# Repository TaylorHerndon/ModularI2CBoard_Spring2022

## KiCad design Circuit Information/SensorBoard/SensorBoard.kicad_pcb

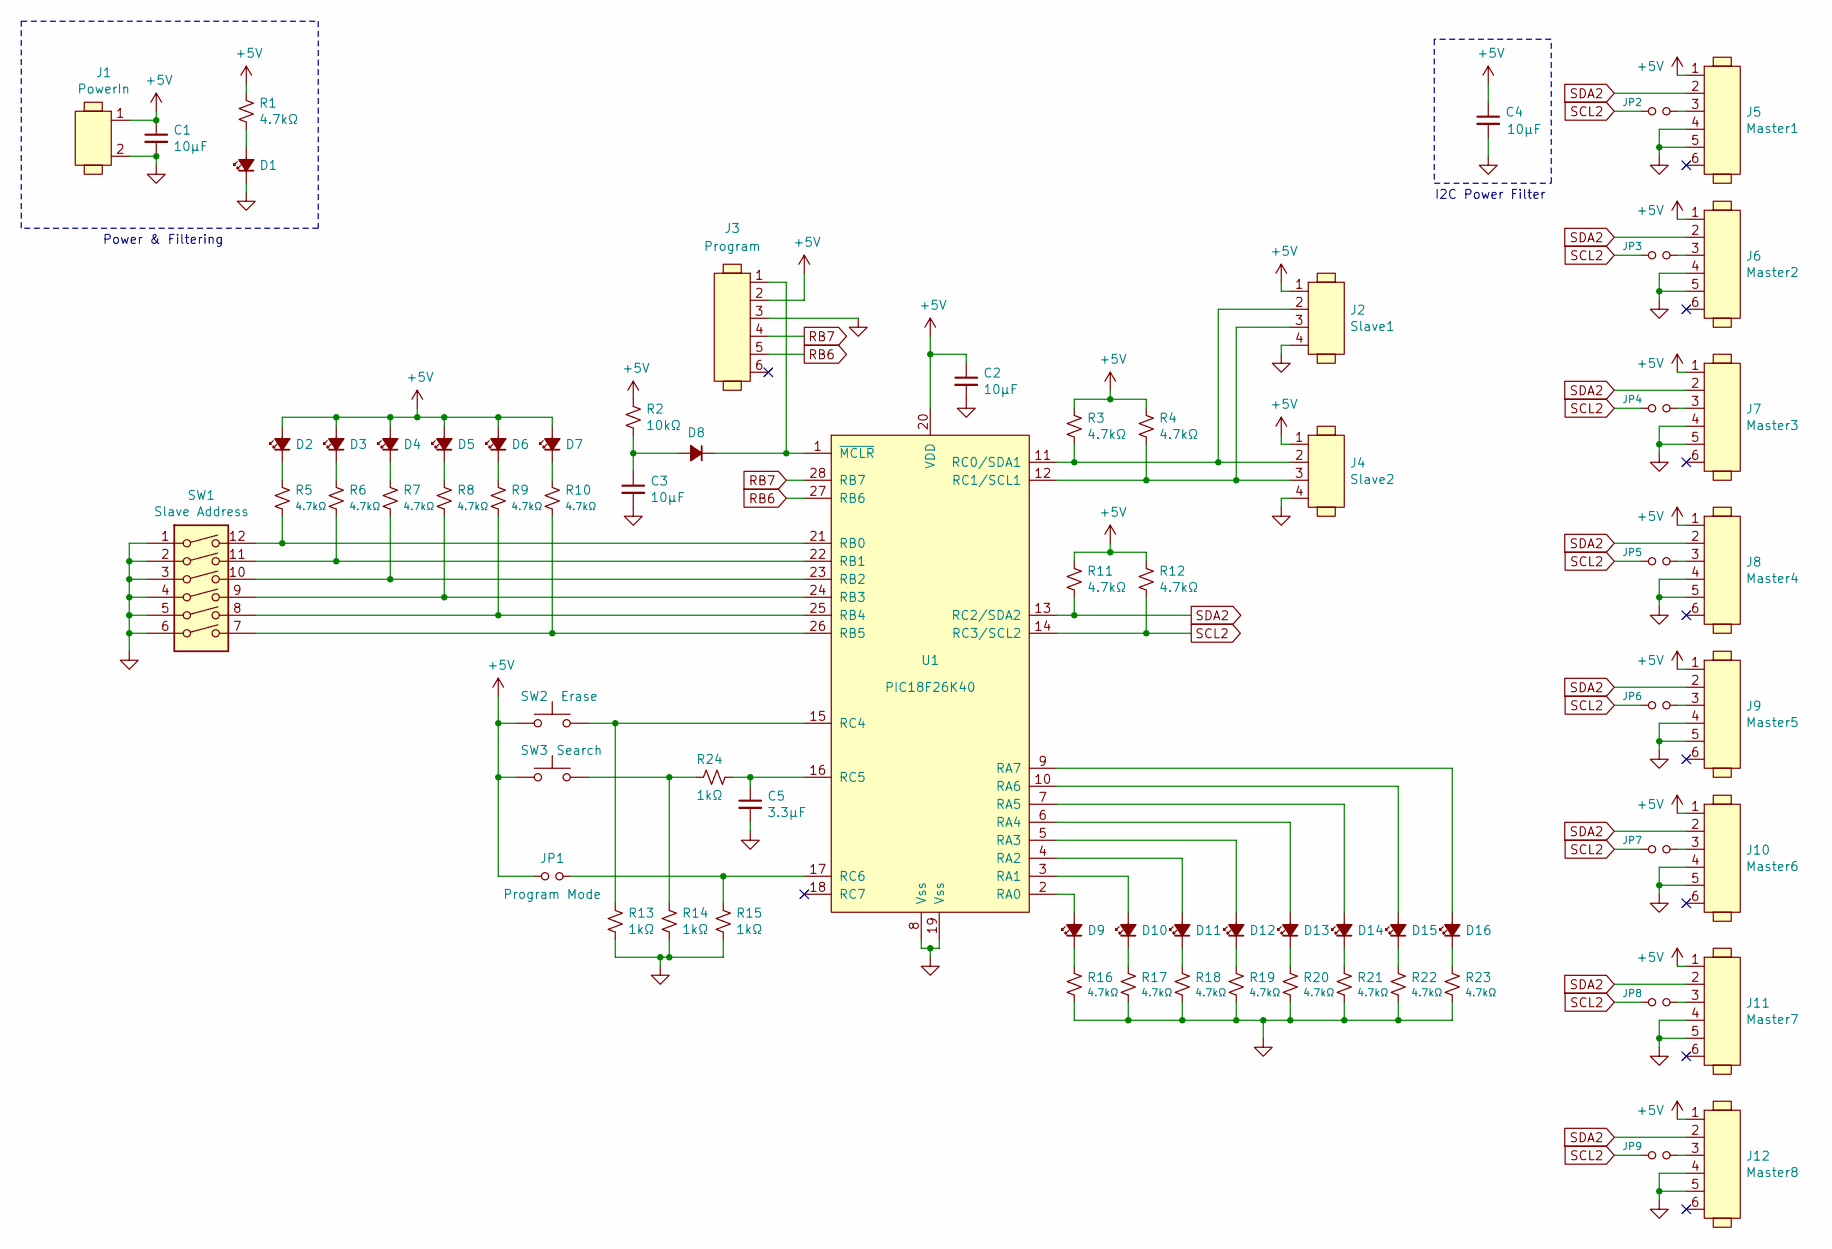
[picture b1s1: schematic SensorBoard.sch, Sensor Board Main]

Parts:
C1, C2, C3, C4: 10µF; R_0805_2012Metric_Pad1.20x1.40mm_HandSolder
C5: 3.3µF; R_0805_2012Metric_Pad1.20x1.40mm_HandSolder
D1, D2, D3, D4, D5, D6, D7, D9, D10, D11, D12, D13, D14, D15, D16: LED_Small_ALT; D_0805_2012Metric
D8: D_Small_ALT; D_0805_2012Metric
J1: PowerIn; 2PinScrewTerminal
J2: Slave1; Molex_KK-254_AE-6410-04A_1x04_P2.54mm_Vertical
J3: Program; PinHeader_1x06_P2.54mm_Vertical
J4: Slave2; Molex_KK-254_AE-6410-04A_1x04_P2.54mm_Vertical
J5: Master1; Molex_KK-254_AE-6410-06A_1x06_P2.54mm_Vertical
J6: Master2; Molex_KK-254_AE-6410-06A_1x06_P2.54mm_Vertical
J7: Master3; Molex_KK-254_AE-6410-06A_1x06_P2.54mm_Vertical
J8: Master4; Molex_KK-254_AE-6410-06A_1x06_P2.54mm_Vertical
J9: Master5; Molex_KK-254_AE-6410-06A_1x06_P2.54mm_Vertical
J10: Master6; Molex_KK-254_AE-6410-06A_1x06_P2.54mm_Vertical
J11: Master7; Molex_KK-254_AE-6410-06A_1x06_P2.54mm_Vertical
J12: Master8; Molex_KK-254_AE-6410-06A_1x06_P2.54mm_Vertical
JP1: Program Mode; PinHeader_1x02_P2.54mm_Vertical
JP2, JP3, JP4, JP5, JP6, JP7, JP8, JP9: Jumper_NO_Small; PinHeader_1x02_P2.54mm_Vertical
R1, R3, R4, R5, R6, R7, R8, R9, R10, R11, R12, R16, R17, R18, R19, R20, R21, R22, R23: 4.7kΩ; R_0805_2012Metric_Pad1.20x1.40mm_HandSolder
R2: 10kΩ; R_0805_2012Metric_Pad1.20x1.40mm_HandSolder
R13, R14, R15, R24: 1kΩ; R_0805_2012Metric_Pad1.20x1.40mm_HandSolder
SW1: Slave Address; SW_DIP_SPSTx06_Slide_9.78x17.42mm_W7.62mm_P2.54mm
SW2: Erase; SW_PUSH_6mm
SW3: Search; SW_PUSH_6mm
U1: PIC18F26K40; PIC18F26K40-SOIC-28

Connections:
+5V: C1.1, C2.1, C4.1, D2.2 (A), D3.2 (A), D4.2 (A), D5.2 (A), D6.2 (A), D7.2 (A), J1.1, J2.1, J3.2, J4.1, J5.1, J6.1, J7.1, J8.1, J9.1, J10.1, J11.1, J12.1, JP1.1, R1.1, R2.1, R3.1, R4.1, R11.1, R12.1, SW2.1, SW3.1, U1.20 (VDD)
GND: C1.2, C2.2, C3.2, C4.2, C5.2, D1.1 (K), J1.2, J2.4, J3.3, J4.4, J5.4, J5.5, J6.4, J6.5, J7.4, J7.5, J8.4, J8.5, J9.4, J9.5, J10.4, J10.5, J11.4, J11.5, J12.4, J12.5, R13.2, R14.2, R15.2, R16.2, R17.2, R18.2, R19.2, R20.2, R21.2, R22.2, R23.2, SW1.1, SW1.2, SW1.3, SW1.4, SW1.5, SW1.6, U1.8 (Vss), U1.19 (Vss)
unnamed: C3.1, D8.2 (A), R2.2
unnamed: C5.1, R24.2, U1.16 (RC5)
unnamed: D1.2 (A), R1.2
unnamed: D2.1 (K), R5.1
unnamed: D3.1 (K), R6.1
unnamed: D4.1 (K), R7.1
unnamed: D5.1 (K), R8.1
unnamed: D6.1 (K), R9.1
unnamed: D7.1 (K), R10.1
unnamed: D8.1 (K), J3.1, U1.1 (~MCLR)
unnamed: D9.1 (K), R16.1
unnamed: D9.2 (A), U1.2 (RA0)
unnamed: D10.1 (K), R17.1
unnamed: D10.2 (A), U1.3 (RA1)
unnamed: D11.1 (K), R18.1
unnamed: D11.2 (A), U1.4 (RA2)
unnamed: D12.1 (K), R19.1
unnamed: D12.2 (A), U1.5 (RA3)
unnamed: D13.1 (K), R20.1
unnamed: D13.2 (A), U1.6 (RA4)
unnamed: D14.1 (K), R21.1
unnamed: D14.2 (A), U1.7 (RA5)
unnamed: D15.1 (K), R22.1
unnamed: D15.2 (A), U1.10 (RA6)
unnamed: D16.1 (K), R23.1
unnamed: D16.2 (A), U1.9 (RA7)
unnamed: J2.2, J4.2, R3.2, U1.11 (RC0/SDA1)
unnamed: J2.3, J4.3, R4.2, U1.12 (RC1/SCL1)
unnamed: J5.3, JP2.2
unnamed: J6.3, JP3.2
unnamed: J7.3, JP4.2
unnamed: J8.3, JP5.2
unnamed: J9.3, JP6.2
unnamed: J10.3, JP7.2
unnamed: J11.3, JP8.2
unnamed: J12.3, JP9.2
unnamed: JP1.2, R15.1, U1.17 (RC6)
unnamed: R5.2, SW1.12, U1.21 (RB0)
unnamed: R6.2, SW1.11, U1.22 (RB1)
unnamed: R7.2, SW1.10, U1.23 (RB2)
unnamed: R8.2, SW1.9, U1.24 (RB3)
unnamed: R9.2, SW1.8, U1.25 (RB4)
unnamed: R10.2, SW1.7, U1.26 (RB5)
unnamed: R13.1, SW2.2, U1.15 (RC4)
unnamed: R14.1, R24.1, SW3.2
RB6: J3.5, U1.27 (RB6)
RB7: J3.4, U1.28 (RB7)
SCL2: JP2.1, JP3.1, JP4.1, JP5.1, JP6.1, JP7.1, JP8.1, JP9.1, R12.2, U1.14 (RC3/SCL2)
SDA2: J5.2, J6.2, J7.2, J8.2, J9.2, J10.2, J11.2, J12.2, R11.2, U1.13 (RC2/SDA2)

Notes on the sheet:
I2C Power Filter
Power & Filtering

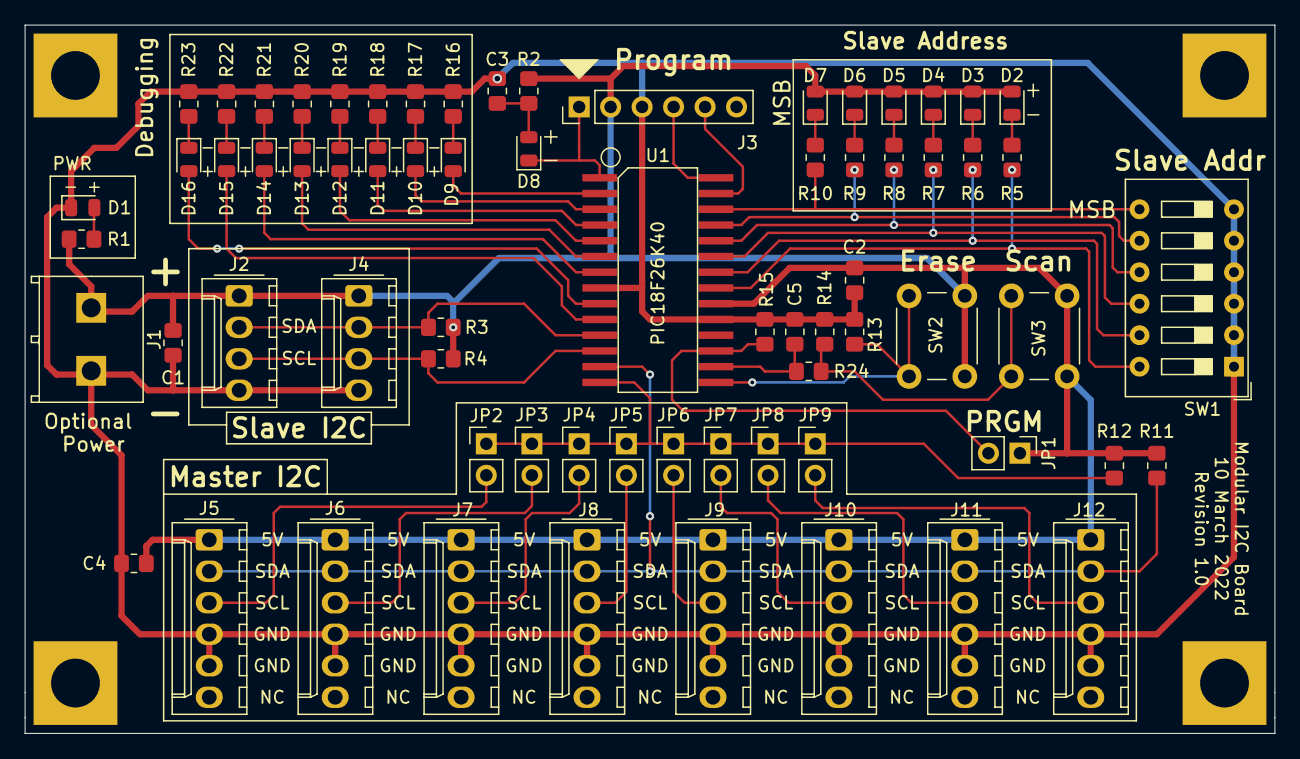
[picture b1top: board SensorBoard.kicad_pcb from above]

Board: 2 copper layers, 100.8 x 57.2 mm, 70 parts (0 on the bottom side), 51 nets.

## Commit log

2022-05-01 Create Configuration Process.pdf
    Added Config Process File
2022-05-01 Added Code and Circuit Information
    ^
